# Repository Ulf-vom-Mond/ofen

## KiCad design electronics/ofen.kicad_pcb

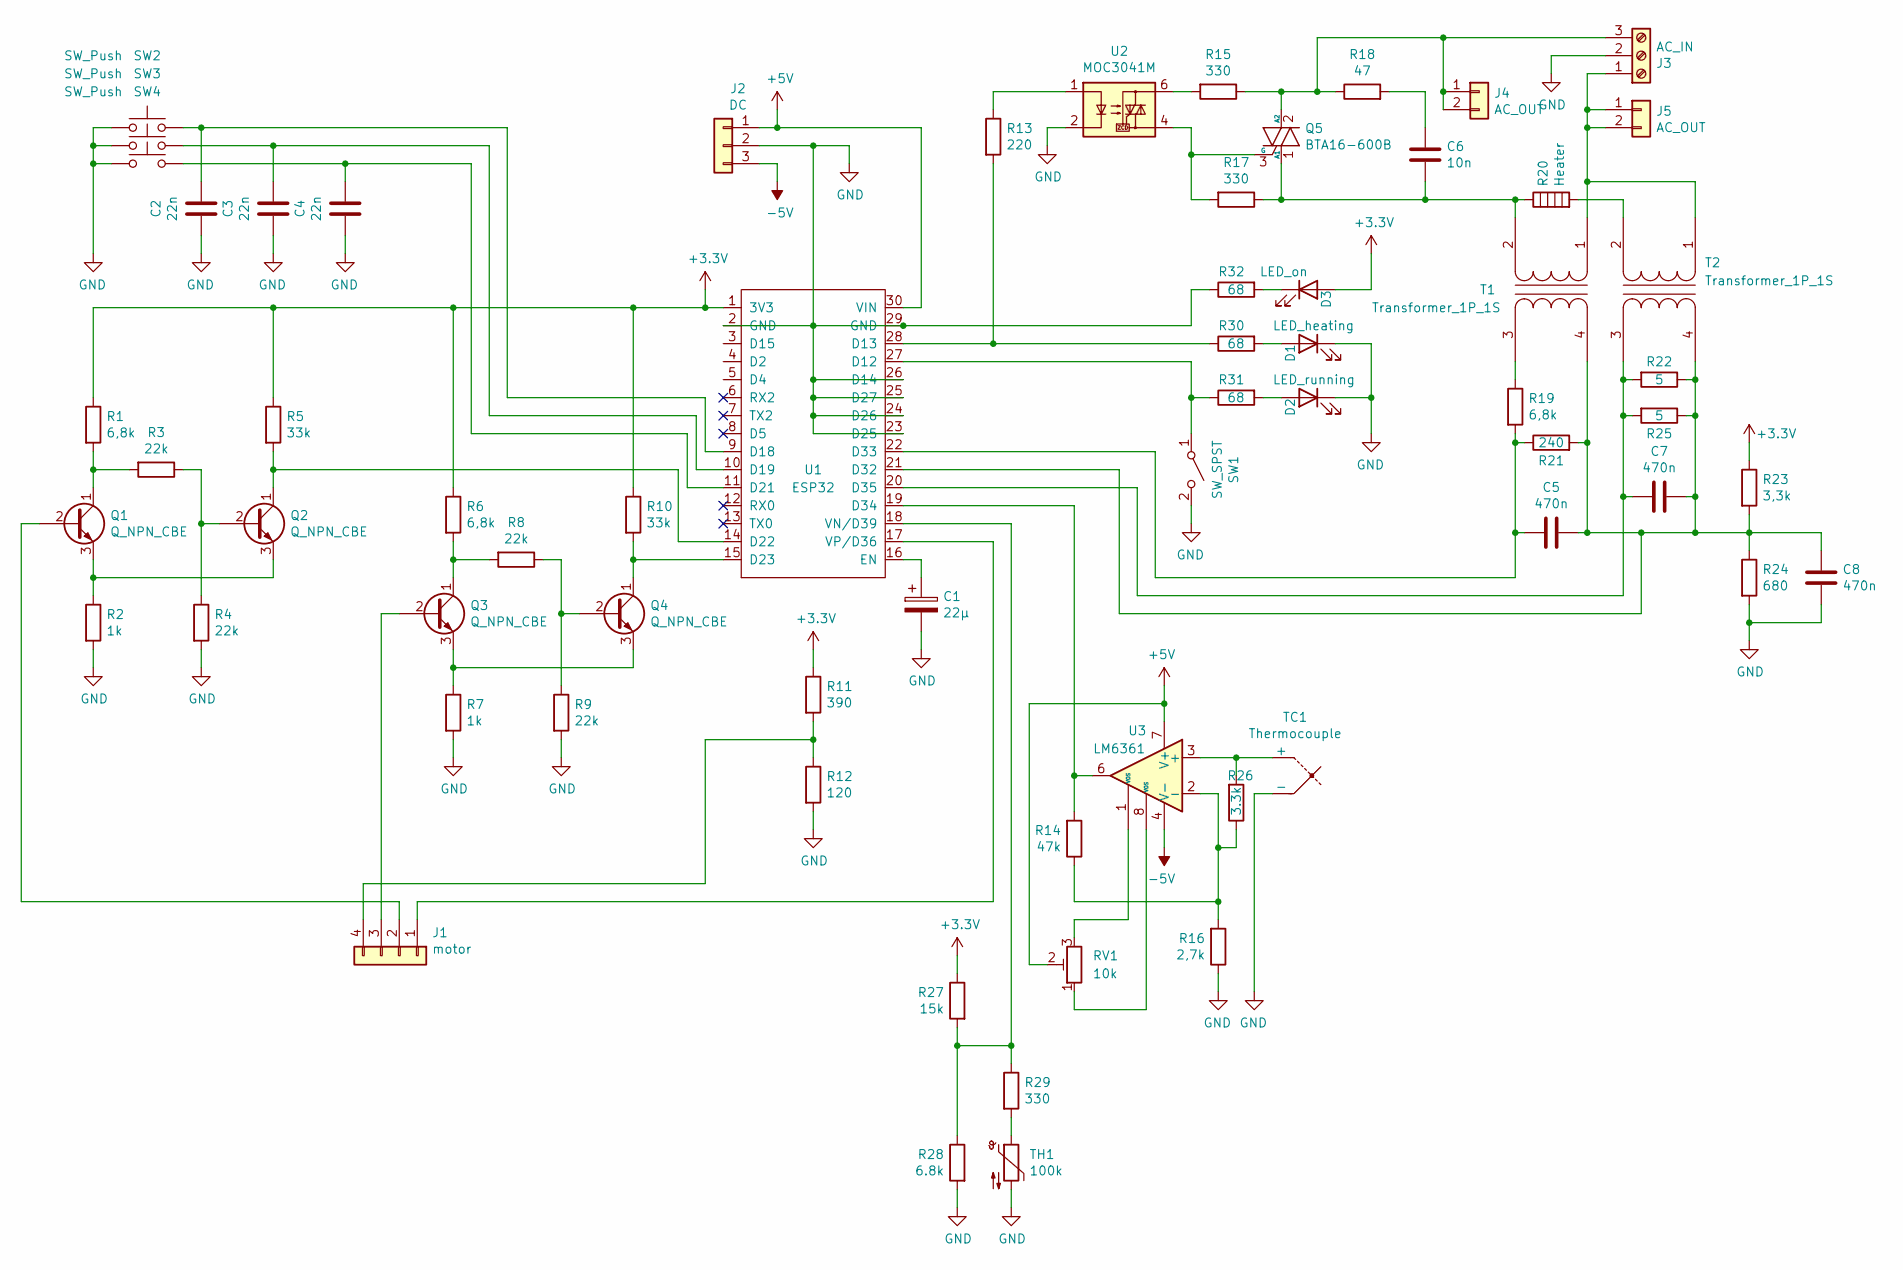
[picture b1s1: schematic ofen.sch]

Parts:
C1: 22µ; CP_Radial_D6.3mm_P2.50mm
C2, C3, C4: 22n; C_Disc_D4.3mm_W1.9mm_P5.00mm
C5, C7, C8: 470n; C_Rect_L7.0mm_W4.5mm_P5.00mm
C6: 10n; C_Rect_L11.5mm_W3.5mm_P10.00mm_MKT
D1: LED_heating; PinHeader_1x02_P2.54mm_Vertical
D2: LED_running; PinHeader_1x02_P2.54mm_Vertical
D3: LED_on; PinHeader_1x02_P2.54mm_Vertical
J1: motor; PinHeader_1x04_P2.54mm_Vertical
J2: DC; PinHeader_1x03_P2.54mm_Vertical
J3: AC_IN; TerminalBlock_Altech_AK300-3_P5.00mm
J4, J5: AC_OUT; SolderWire-0.75sqmm_1x02_P4.8mm_D1.25mm_OD2.3mm
Q1, Q2, Q3, Q4: Q_NPN_CBE; TO-92L_Inline_Wide
Q5: BTA16-600B; SolderWire-0.75sqmm_1x03_P4.8mm_D1.25mm_OD2.3mm
R1, R6, R19: 6,8k; R_Axial_DIN0207_L6.3mm_D2.5mm_P10.16mm_Horizontal
R2, R7: 1k; R_Axial_DIN0207_L6.3mm_D2.5mm_P10.16mm_Horizontal
R3, R4, R8, R9: 22k; R_Axial_DIN0207_L6.3mm_D2.5mm_P10.16mm_Horizontal
R5, R10: 33k; R_Axial_DIN0207_L6.3mm_D2.5mm_P10.16mm_Horizontal
R11: 390; R_Axial_DIN0207_L6.3mm_D2.5mm_P10.16mm_Horizontal
R12: 120; R_Axial_DIN0207_L6.3mm_D2.5mm_P10.16mm_Horizontal
R13: 220; R_Axial_DIN0207_L6.3mm_D2.5mm_P10.16mm_Horizontal
R14: 47k; R_Axial_DIN0207_L6.3mm_D2.5mm_P10.16mm_Horizontal
R15, R17, R29: 330; R_Axial_DIN0207_L6.3mm_D2.5mm_P10.16mm_Horizontal
R16: 2,7k; R_Axial_DIN0207_L6.3mm_D2.5mm_P10.16mm_Horizontal
R18: 47; R_Axial_DIN0207_L6.3mm_D2.5mm_P10.16mm_Horizontal
R20: Heater; TerminalBlock_Altech_AK300-3_P5.00mm
R21: 240; R_Axial_DIN0207_L6.3mm_D2.5mm_P10.16mm_Horizontal
R22, R25: 5; R_Axial_DIN0207_L6.3mm_D2.5mm_P10.16mm_Horizontal
R23: 3,3k; R_Axial_DIN0207_L6.3mm_D2.5mm_P10.16mm_Horizontal
R24: 680; R_Axial_DIN0207_L6.3mm_D2.5mm_P10.16mm_Horizontal
R26: 3.3k; R_Axial_DIN0207_L6.3mm_D2.5mm_P10.16mm_Horizontal
R27: 15k; R_Axial_DIN0207_L6.3mm_D2.5mm_P10.16mm_Horizontal
R28: 6.8k; R_Axial_DIN0207_L6.3mm_D2.5mm_P10.16mm_Horizontal
R30, R31, R32: 68; R_Axial_DIN0207_L6.3mm_D2.5mm_P10.16mm_Horizontal
RV1: 10k; Potentiometer_Bourns_3296W_Vertical
SW1: SW_SPST; PinHeader_1x02_P2.54mm_Vertical
SW2, SW3, SW4: SW_Push; PinHeader_1x02_P2.54mm_Vertical
T1, T2: Transformer_1P_1S; SolderWire-0.75sqmm_1x04_P4.8mm_D1.25mm_OD2.3mm
TC1: Thermocouple; PinHeader_1x02_P2.54mm_Vertical
TH1: 100k; PinHeader_1x02_P2.54mm_Vertical
U1: ESP32; ESP32-DevModule
U2: MOC3041M; DIP-6_W7.62mm_Socket_LongPads
U3: LM6361; DIP-8_W7.62mm_Socket_LongPads

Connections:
+3V3: D3.2 (A), R1.1, R5.1, R6.1, R10.1, R11.1, R23.1, R27.1, U1.1 (3V3)
+5V: J2.1, RV1.2, U1.30 (VIN), U3.7 (V+)
-5V: J2.3, U3.4 (V-)
GND: C1.2, C2.1, C3.1, C4.1, C8.1, D1.1 (K), D2.1 (K), J2.2, J3.2, R2.2, R4.2, R7.2, R9.2, R12.2, R16.1, R24.2, R28.2, R32.1, SW1.2 (B), SW2.2, SW3.2, SW4.2, TC1.2 (-), TH1.2, U1.2 (GND), U1.23 (D25), U1.24 (D26), U1.25 (D27), U1.26 (D14), U1.29 (GND), U2.2; also elsewhere on the board
unnamed: C1.1, U1.16 (EN)
unnamed: C2.2, SW2.1, U1.9 (D18)
unnamed: C3.2, SW3.1, U1.10 (D19)
unnamed: C4.2, SW4.1, U1.11 (D21)
unnamed: C5.1, C7.1, C8.2, R21.2, R22.1, R23.2, R24.1, R25.1, T1.4 (SB), T2.4 (SB), U1.21 (D32)
unnamed: C5.2, R19.2, R21.1, U1.22 (D33)
unnamed: C6.1, R18.2
unnamed: C6.2, Q5.1 (A1), R17.1, R20.1, T1.2 (AB)
unnamed: C7.2, R22.2, R25.2, T2.3 (SA), U1.20 (D35)
unnamed: D1.2 (A), R30.2
unnamed: D2.2 (A), R31.2
unnamed: D3.1 (K), R32.2
unnamed: J1.1, U1.17 (VP/D36)
unnamed: J1.2, Q1.2 (B)
unnamed: J1.3, Q3.2 (B)
unnamed: J1.4, R11.2, R12.1
unnamed: J3.1, J5.1, J5.2, T1.1 (AA), T2.1 (AA)
unnamed: J3.3, J4.1, J4.2, Q5.2 (A2), R15.1, R18.1
unnamed: Q1.1 (C), R1.2, R3.2
unnamed: Q1.3 (E), Q2.3 (E), R2.1
unnamed: Q2.1 (C), R5.2, U1.14 (D22)
unnamed: Q2.2 (B), R3.1, R4.1
unnamed: Q3.1 (C), R6.2, R8.2
unnamed: Q3.3 (E), Q4.3 (E), R7.1
unnamed: Q4.1 (C), R10.2, U1.15 (D23)
unnamed: Q4.2 (B), R8.1, R9.1
unnamed: Q5.3 (G), R17.2, U2.4
unnamed: R13.1, U2.1
unnamed: R13.2, R30.1, U1.28 (D13)
unnamed: R14.1, R16.2, R26.1, U3.2 (-)
unnamed: R14.2, U1.19 (D34), U3.6
unnamed: R15.2, U2.6
unnamed: R19.1, T1.3 (SA)
unnamed: R20.2, T2.2 (AB)
unnamed: R26.2, TC1.1 (+), U3.3 (+)
unnamed: R27.2, R28.1, R29.1, U1.18 (VN/D39)
unnamed: R29.2, TH1.1
unnamed: R31.1, SW1.1 (A), U1.27 (D12)
unnamed: RV1.1, U3.8 (VOS)
unnamed: RV1.3, U3.1 (VOS)

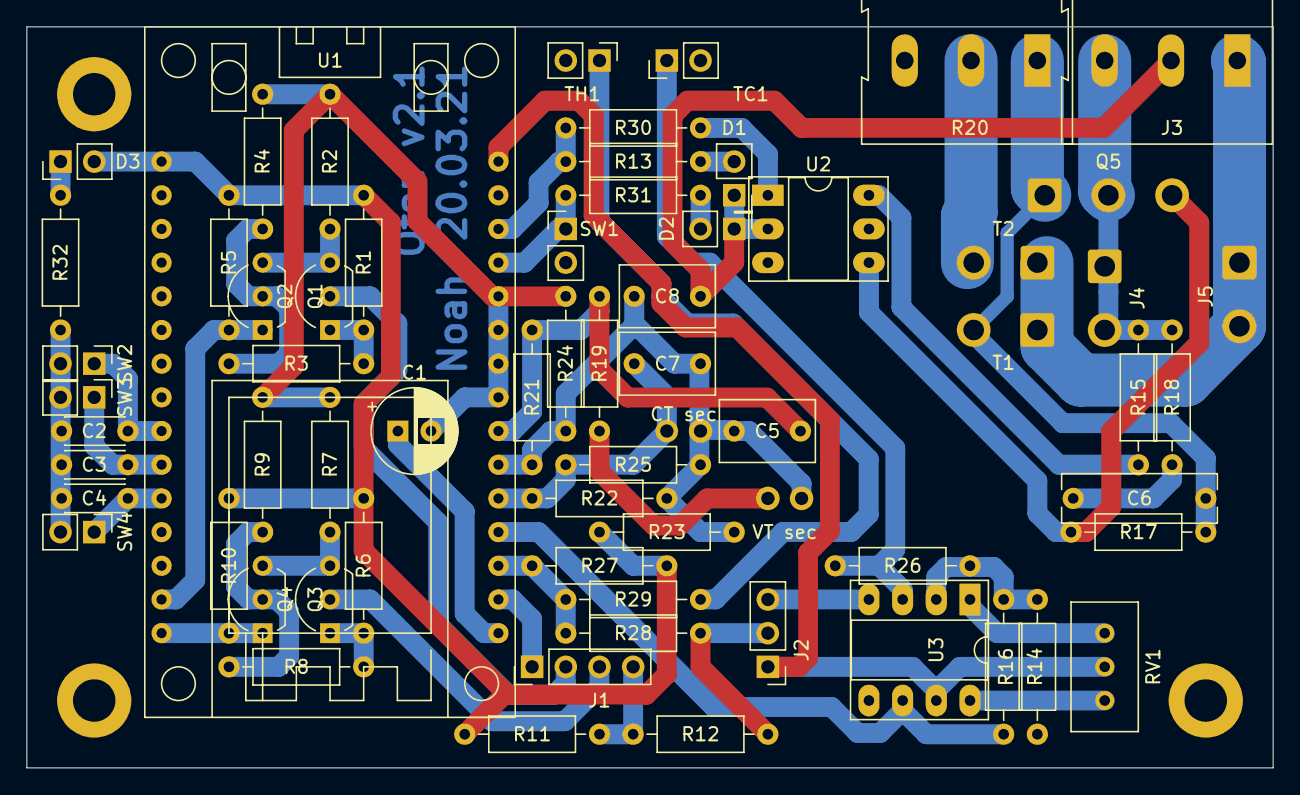
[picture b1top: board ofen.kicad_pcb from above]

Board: 2 copper layers, 94.0 x 55.9 mm, 68 parts (0 on the bottom side), 44 nets.

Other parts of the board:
 : MountingHole_3.2mm_M3_DIN965_Pad
 #2,  #3: MountingHole_3.2mm_M3_DIN965_Pad

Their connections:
GND: .1, #2.1, #3.1; also elsewhere on the board

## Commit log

2020-11-14 initila commit
2020-11-14 added some things to .gitignore
2020-11-15 first part of the display works (time, temperature and power display)
2020-11-21 drawing of coordinate system + axis annotation works. wrote method to draw lines + connect them apropriately
2020-11-21 table gets filled and graph drawing works
2020-12-30 splitted display into static and dynamic part to increase performance
2020-12-31 highlighting selected number works
2020-12-31 fixed severer bugs with drawing of graph and table and with changing values
2020-12-31 deleteing by long press works now
2020-12-31 forgot some mess lurking around
2021-01-01 got rid of all the \u001A characters and used thin lines for separation lines and coordinate system.
2021-01-01 ICH HASSE MICH
2021-01-01 dont hate myself anymore. fixed a lo of terrible things. Significant changes: PID prepared, PWM works, On/Off seems to work, on-time timer is counting, setting temp according to setpoints works
2021-01-09 everything broken now
2021-01-10 i did really horrible things but somehow it kinda works now. i dont why. but i dont care anymore. please just dont break again
2021-01-18 this is a working, but not very usable version
2021-01-22 fixed crashing when turning the knob, improved setpoint deletion
2021-01-24 setpoints get saved in non volatile storage now
2021-01-24 introduced serial commands and pid autotune. should be more or less finished now. missing: thermocouple reference temperature compensation, finetuning of temp and power reading
2021-01-25 made a PCB
2021-01-26 increased ground zone clearance to 0.8mm, updated KiCad version to 5.1.9
2021-01-26 added resistor in parallel to the thermocouple to prevent OpAmp from destroying the ESP32
2021-01-28 arranged silkscreen and symbols properly
2021-02-03 updated gpio configuration according to PCB
2021-03-13 added opamp offset trimmer to schematic and pcb
2021-03-13 redid adc calibration and some small changes
2021-03-16 added cold junction compensation and three status leds
2021-03-18 redesigned PCB. smaller, better, double layer
2021-03-20 removed front GND pour on PCB
2021-03-21 added constantOutput command, improved current and voltage measurement, fixed setpoint save bug
2021-03-21 added GeoGebra files
